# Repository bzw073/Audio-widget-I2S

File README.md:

# Audio-widget-I2S
**Interfata audio USB utilizand un AVR32 pe protocolul I2S**

## Introducere
>
>Inca din timpurile dinaintea erei digitale, consumatorii de audio **asa zisii audiofili** au fost in cautare de metode pentru reducerea la minim a distorsiunilor transmise catre difuzoare,si implicit,percepute de urechea umana.In vremea respectiva,data fiind si complexitatea destul de redusa a dispozitivelor,ideea reducerii distorsiunilor in sisteme era destul de limitata de topologiile propuse,de aceea aparitia sistemelor digitale de procesare in audio a dus la reducerea drastica a neajunsurilor semnalelor analogice.Pentru **puristi** , circuitele digitale si DSP-urile sunt considerate _un sacrilegiu_ adus audiofiliei,dar este unul justificat,deoarece in ciuda complexitatii mai ridicate fata de un circuit analog pur , sistemele digitale sunt mult mai eficiente fata de complementele sale,iar posibilitatea customizarii lor este foarte mare (spre deosebire de un circuit analogic unde,pentru a modifica o caracteristica trebuie regandit tot circuitul,in cazul unui circuit digital cu uC este doar o problema de software).

>Aparitia interfetelor audio s-a facut odata cu dezvoltarea PC-urilor si inregistrarea de muzica/sunete pe medii digitale , in pofida benzilor magnetice si a discurilor de vinil , deoarece era necesara o metoda de redare a sunetelor stocate pe calculatoarele vremii. De altfel,primele asa zise **placi de sunet** si-au facut aparitia prin calculatoare in jurul generatiei 80486 , cand deja exista o oarecare structura de operare stabila pe 16 biti , iar pentru o esantionare simpla a sunetelor erau arhisuficiente instructiunile implementate de Intel in procesoarele respective.
>>_Daca facem referinta la vremurile actuale,se poate spune ca practic nici nu se punea problema de calitate sau termenul de **Hi-Fi** in acele vremuri,dar acele sunete au reprezentat ceea ce urma sa fie boom-ul erei digitale_
>
>Ca si istorie a acestei ere in care traim,se pot scrie foarte multe lucruri deja cunoscute,asa ca voi incerca sa ma concentrez pe esential.

>Ideea de "calitate audio" pe digital a aparut in momentul lansarii pe piata mondiala a CD-ului (acel lucru care acum multora dintre noi ni se pare atat de outdated,ori chiar nu il mai folosim),dar el a avut cea mai mare influenta in aparitia de tehnologii de compresie si codare audio.Ca si concept,ideea de CD a aparut prin anul 1980 ,cand Philips si Sony au incheiat un parteneriat de cercetare in domeniul digital,dorindu-se un mediu de stocare unic transmisibil,care sa aibe un spatiu de stocare a informatiilor mult mai mare decat cel al dischetelor "floppy" si al benzilor magnetice,dar totusi sa nu coste cat un hard disk al vremurilor (memo: un hard disk de tip Winchester avea o capacitate de maxim 128MB , cantarea in jur de 15-20kg si era cam cat un desktop SFF actual ca dimensiuni si costa in jur de ~5.000 de dolari unul?).
>>Standardul CD a fost definitivat in jurul anului 1983,iar in urma intelegerii realizate intre cele 2 concerne se va realiza trecerea industriei audio catre acest mediu.

>Se pune problema "compresiei audio".In a nutshell,algoritmul de compresie audio se refera la un standard de scriere-redare a sunetelor pe calculatoare. Calculatoarele,la momentul respectiv avand sisteme de operare stabile precum UNIX si DOS (vorbind de anii '80,dar regula se aplica si in prezent pe sistemele actuale),pentru a reda sunetele stocate pe medii precum hard-diskul se folosesc de niste software numite **codec** .
>>Codecurile,in esenta,sunt niste pseudo-drivere pe care sistemul de operare le interpreteaza atunci cand se executa in sistem un fisier cu extensia ce corespunde codecului respectiv.
>>Adica,spre exemplu, avem un fisier cu extensia ".mp3" , SO va sti ca la instantierea acestui fisier va trebui sa apeleze un Codec LAME(Lame Ain't an MP3 Encoder - care este o derivatie imbunatatita de-a lungul anilor de diversi programatori din conceptul original gandit de institutul Fraunhofer din Germania).

>De altfel , toate procedeele de redare/compresie si extensiile de sistem au fost posibile datorita codarii PCM (Pulse Code Modulation).
PCM reprezinta transformarea semnalelor analogice in semnale digitale printr-un algoritm de esantionare constanta a amplitudinii semnalului analogic ,iar fiecare esantion este cuantizat la cea mai apropiata valoare dintr-o gama de cuante apropiate.
>>**Codarea PCM prezinta 2 proprietati ce determina calitatea conversiei semnalului original raportat la acesta : rata de esantionare a semnalului si _bit depth_,care reprezinta cantitatea de biti al fiecarui esantion realizat (un CD-Audio prezinta un bit depth de 16 biti per esantion , pe cand un Blu-ray sau DVD-Audio 24 de biti per esantion).**
>>> Extensiile posibile unei compresii PCM sunt ".wav" ,".L16",".PCM",".AIFF",".AU"

>Pe baza codarii/compresiei PCM a fisierelor audio, cei de la Philips au realizat in anul 1986 (si ulterior revizuit in 1996) un protocol de transmisie seriala al datelor audio intre dispozitive / circuite integrate , protocol care inca se foloseste cu succes si in prezent in dispozitivele audio. Este cunoscut sub acronimul I2S sau IIS **Inter-IC Sound** si se bazeaza pe o magistrala sincrona de transmisie de date (clockul de transmisie intre circuite este separat de magistrala de date,deci implicit receptorul nu mai are nevoie de un circuit suplimentar de refacere a frontului de ceas trimis de emitator).
>Protocolul este relativ usor de interpretat, in principal avem de-a face cu 3 semnale : bit clock line(**BCLK**) , word clock line (cunoscut sub denumirea oficiala de 'word select' **WS** sau 'left-right clock' **LRCLK** ) si cel putin o linie de date multiplexata **SD**

>>Adeseori se mai poate intalni peste cele 3 semnale cunoscute inca un semnal de tact (care nu face parte din protocol) cu rolul de a sincroniza operatiile interne ale DAC-urilor cu cele ale controllerului . Este gasit sub acronimul de "Master clock" **MCLK**
>>>Frecventa tipica de lucru se calculeaza dupa formula : **MCLK = 256 * LRCLK**

###### Cum functioneaza protocolul:

>Semnalul de "Word Select" permite dispozitivului receptor sa 'vada' ce canal urmeaza sa fie trimis , deoarece I2S permite ca pe aceeasi linie de date sa fie trimise 2 canale,fiind un semnal cu factor de umplere 50% si frecventa egala cu cea de esantionare a semnalului trimis.
>>**Pentru semnale stereo , in brosura de specificatii a I2S se spune ca semnalul audio de pe canalul stang se transmite pe palierul de 0 al Word Select , iar canalul drept pe palierul de 1 . De obicei , semnalul "Word Select" este sincronizat dupa fronturile cazatoare ale semnalului BCLK , deoarece datele sunt zavorate pe fronturile crescatoare**.
>>
>Se stabileste semnul liniei de date si se codeaza in complement fata de 2 cu primul bit MSB-ul . **Acest lucru permite ca numarul de biti per cadru sa fie arbitrar , fara a fi nevoie de "negociere" intre emitator si receptor **.

## Specificatii montaj:

1.
 a)Microcontroller utilizat:  Atmel AT32UC3A3256 
 >>>  A complete system-on-chip 32-bit AVR microcontroller. It is designed for cost-sensitive embedded applications that require low power consumption, high code density and high performance.

 >>> The microcontroller's Memory Protection Unit (MPU) and fast, flexible interrupt controller support the latest real-time operating systems. Higher computation capabilities are achievable using a rich set of DSP instructions. The device incorporates on-chip flash and SRAM memories for secure and fast access. 64 KBytes of SRAM are directly coupled to the 32-bit AVR UC3 for performance optimization. Two blocks of 32 Kbytes SRAM are independently attached to the high speed bus matrix for real ping-pong management.

 >>> The microcontroller achieves exceptionally high data throughput by combining the multi-layered 32-bit AVR databus,128 KB on-chip SRAM with triple high speed interfaces, multi-channel peripheral, memory-to-memory DMA controller, high-speed USB embedded host, SD/SDIO card, MLC NAND flash with ECC, and SDRAM interfaces.

 >>> This device features 256KB internal high-speed flash and full-duplex multi-channel I2S audio interface.
 
 b) DAC utilizat: PCM5102A

 >>>The PCM510xA devices are a family of monolithic CMOS-integrated circuits that include a stereo digital-to-analog converter and additional support circuitry in a small TSSOP package. The PCM510xA devices use the latest generation of TI’s advanced segment-DAC architecture to achieve excellent dynamic performance and improved tolerance to clock jitter.

 c) Amplificator/buffer iesire folosit : TPA6120
 >>>In applications requiring a high-power output, very high fidelity headphone amplifier, the TPA6120A2 replaces a costly discrete design and allows music, not the amplifier, to be heard. The TPA6120A2’s current-feedback AB amplifier architecture delivers high bandwidth, extremely low noise, and up to 128dB of dynamic range.
 
2.Utilizeaza USB Audio Class 1 / 2.

3.Capabilitati de redare audio pana la 24bit/96kHz (bit depth / sampling rate).

4.Tensiune de alimentare: 5V

5.Consum max: 500mA 

### Constructie montaj:

Contructia se bazeaza pe un design modular , iar in acest sens voi concepe intregul sistem pe 4 placi:
 - una o va constitui interfata emulatoare usb-i2s
 - o placa pentru DAC si , eventual , buffere de iesire
 - o placa pentru amplificatorul final
 - o placa pentru alimentare suplimentara

Ideea conceperii montajului intr-un sistem modular este pentru imbunatatirea "lantului" pe decursul timpului (ex. realizarea unui DAC mai performant din perspectiva SNR / PSRR sau schimbarea unei surse liniare cu una in comutatie sau adaugarea de acumulatori pentru portabilitate etc.)

De altfel,un montaj modular poate presupune o asezare mai buna in cutie si,totodata, un ecranaj mai bun al partilor **mai sensibile** fata de circuitul de alimentare.

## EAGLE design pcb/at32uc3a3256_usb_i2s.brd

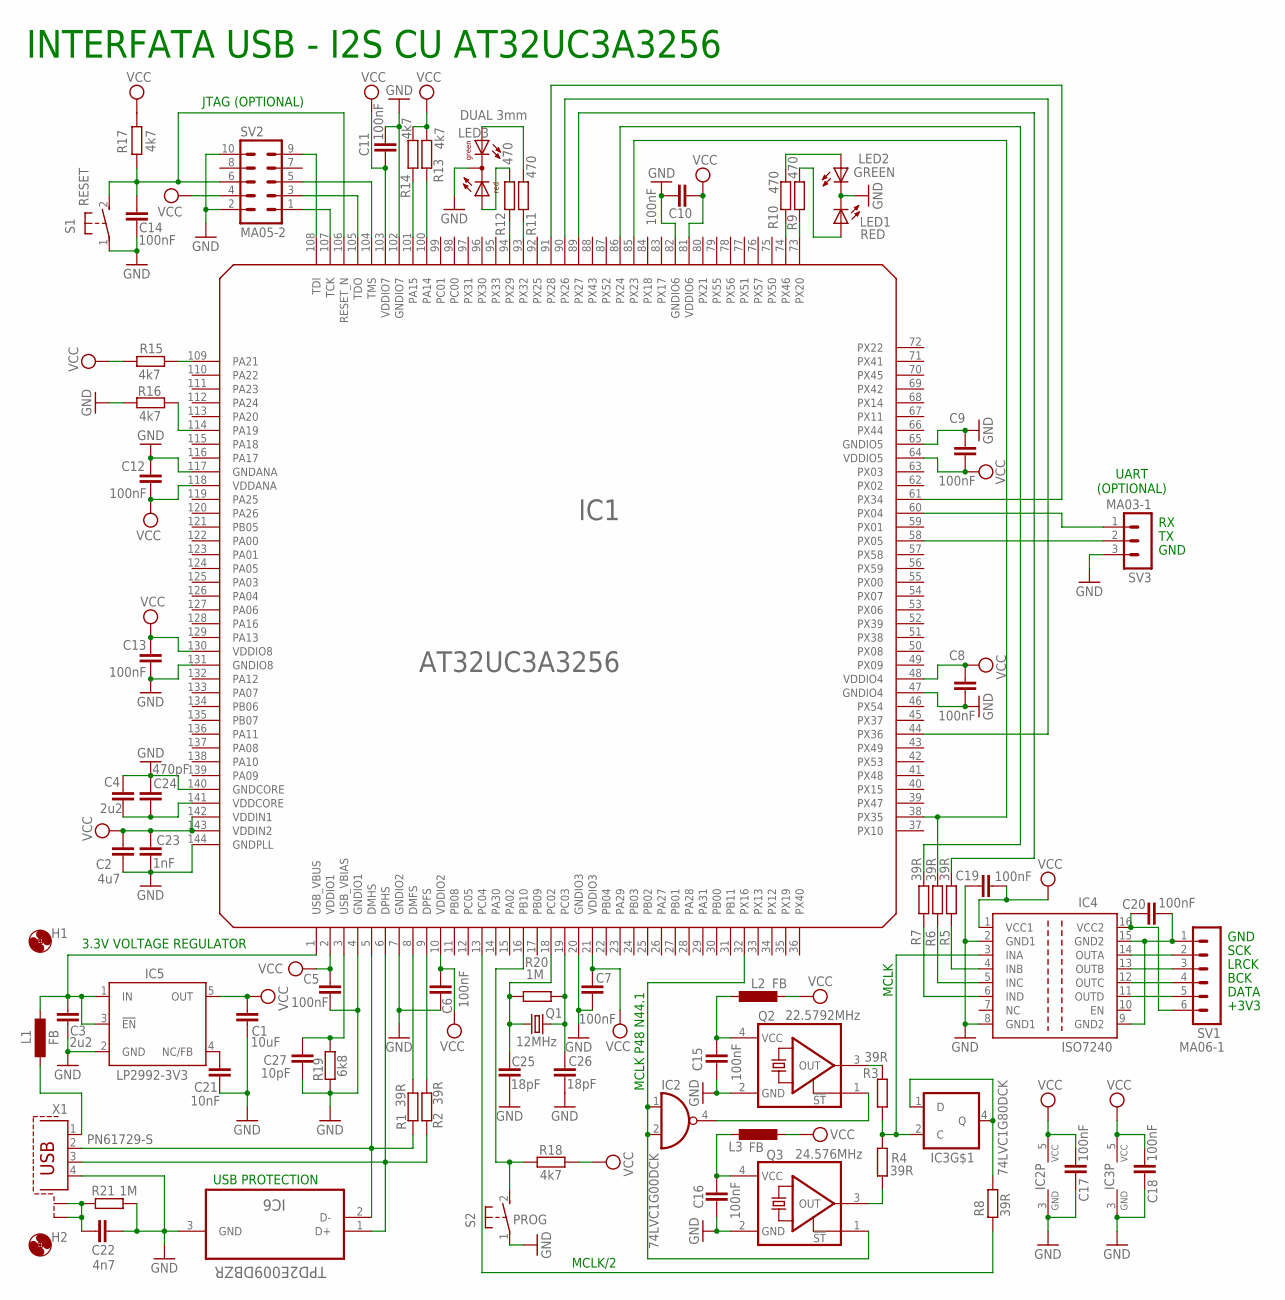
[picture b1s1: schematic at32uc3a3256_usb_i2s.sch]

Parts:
C1: 10uF; C0603
C2: 4u7; C0603
C3, C4: 2u2; C0603
C5, C6, C7, C8, C9, C10, C11, C12, C13, C14, C15, C16, C17, C18, C19, C20: 100nF; C0603
C21: 10nF; C0603
C22: 4n7; C0603
C23: 1nF; C0603
C24: 470pF; C0603
C25, C26: 18pF; C0603
C27: 10pF; C0603
H1, H2: MOUNT-HOLE3.2; 3,2
IC1: AT32UC3A3256; LQFP144
IC2: 74LVC1G00DCK; SC70-5
IC3: 74LVC1G80DCK; SC70-5
IC4: ISO7240; SO-16DW
IC5: LP2992-3V3; SOT23-DBV
IC6: TPD2E009DBZR; SOT95P237X112-3N
L1, L2, L3: FB; L2012C
LED1: RED; CHIPLED_0603
LED2: GREEN; CHIPLED_0603
LED3: DUAL 3mm; DUOLED5MM
Q1: 12MHz; CTS406
Q2: 22.5792MHz; CRYSTAL2.5X2
Q3: 24.576MHz; CRYSTAL2.5X2
R1, R2, R3, R4, R5, R6, R7, R8: 39R; R0603
R9, R10, R11, R12: 470; R0603
R13, R14, R15, R16, R17, R18: 4k7; R0603
R19: 6k8; R0603
R20, R21: 1M; R0603
S1: RESET; SWITCH-KSR
S2: PROG; SWITCH-KSR
SV1: MA06-1
SV2: MA05-2
SV3: MA03-1
X1: PN61729-S

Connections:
AD_LRCK: IC1.44 (PX36), IC1.90 (PX26)
AD_SCLK: IC1.61 (PX34), IC1.91 (PX28)
DA_LRCK: IC1.89 (PX27), R5.2
DA_SCLK: IC1.38 (PX35), IC1.85 (PX23), R6.2
GND: C1.2, C2.2, C3.2, C4.1, C5.2, C6.2, C7.2, C8.2, C9.1, C10.1, C11.1, C12.1, C13.1, C14.2, C15.1, C16.1, C17.2, C18.2, C19.1, C21.2, C22.2, C23.2, C24.1, C25.2, C26.2, C27.2, IC1.4 (GNDIO1), IC1.7 (GNDIO2), IC1.20 (GNDIO3), IC1.47 (GNDIO4), IC1.65 (GNDIO5), IC1.82 (GNDIO6), IC1.102 (GNDIO7), IC1.117 (GNDANA), IC1.131 (GNDIO8), IC1.140 (GNDCORE), IC1.144 (GNDPLL), IC2.3 (GND), IC3.3 (GND), IC4.2 (GND1), IC4.8 (GND1), IC5.2 (GND), IC6.3 (GND), LED1.C, LED2.C, LED3.K (C), Q2.2 (GND), Q3.2 (GND), R16.1, R19.1, R21.2, S1.1, S2.1, SV2.2, SV2.10, SV3.3, X1.4
GND2: C20.2, IC4.9 (GND2), IC4.15 (GND2), SV1.1
GPIO_05_LED2: IC1.94 (PX29), R12.1
GPIO_08_LED1: IC1.93 (PX32), R11.1
LRCK: IC4.4 (INB), R5.1
MCLK: IC3.2 (C), IC4.3 (INA), R3.1, R4.2
MCLK_MCU: IC1.13 (PC04), R8.1
MCLK_P48_N441: IC1.32 (PX16), IC2.1 (I0), IC2.2 (I1), Q3.1 (!ST)
unnamed: C15.2, L2.2, Q2.4 (VCC)
unnamed: IC1.5 (DMHS), IC6.2 (D-), R1.1, X1.2
unnamed: Q3.3 (OUT), R4.1
unnamed: Q2.3 (OUT), R3.2
unnamed: C16.2, L3.2, Q3.4 (VCC)
unnamed: IC1.6 (DPHS), IC6.1 (D+), R2.1, X1.3
unnamed: IC1.8 (DMFS), R1.2
unnamed: C26.1, IC1.19 (PC03), Q1.3 (2), R20.2
unnamed: C25.1, IC1.18 (PC02), Q1.1, R20.1
unnamed: IC1.9 (DPFS), R2.2
unnamed: C4.2, C24.2, IC1.141 (VDDCORE)
unnamed: IC1.108 (TDI), SV2.9
unnamed: IC1.114 (PA19), R16.2
unnamed: C22.1, R21.1, X1.S1, X1.S2
unnamed: C27.1, IC1.3 (USB_VBIAS), R19.2
unnamed: C20.1, IC4.16 (VCC2), SV1.6
unnamed: IC4.14 (OUTA), SV1.2
unnamed: IC4.13 (OUTB), SV1.3
unnamed: IC4.12 (OUTC), SV1.4
unnamed: LED1.A, R9.2
unnamed: LED2.A, R10.2
unnamed: IC1.74 (PX46), R10.1
unnamed: IC1.73 (PX20), R9.1
unnamed: IC1.109 (PA21), R15.2
unnamed: IC1.101 (PA15), R14.1
unnamed: IC1.100 (PA14), R13.1
unnamed: IC4.11 (OUTD), SV1.5
unnamed: IC4.5 (INC), R6.1
unnamed: IC1.86 (PX24), R7.2
unnamed: IC4.6 (IND), R7.1
unnamed: IC3.1 (D), IC3.4 (Q), R8.2
unnamed: L1.1, X1.1
unnamed: LED3.AG, R11.2
unnamed: C21.1, IC5.4 (NC/FB)
unnamed: LED3.AR, R12.2
unnamed: IC2.4 (O), Q2.1 (!ST)
NSRST: C14.1, IC1.106 (RESET_N), R17.1, S1.2, SV2.6
PROG: IC1.16 (PB10), R18.2, S2.2
TCK: IC1.107 (TCK), SV2.1
TDO: IC1.105 (TDO), SV2.3
TMS: IC1.104 (TMS), SV2.5
UART_RX: IC1.60 (PX04), SV3.1
UART_TX: IC1.58 (PX05), SV3.2
VBUS: C3.1, IC1.1 (USB_VBUS), IC5.1 (IN), IC5.3 (!EN), L1.2
VCC: C1.1, C2.1, C5.1, C6.1, C7.1, C8.1, C9.2, C10.2, C11.2, C12.2, C13.2, C17.1, C18.1, C19.2, C23.1, IC1.2 (VDDIO1), IC1.10 (VDDIO2), IC1.21 (VDDIO3), IC1.48 (VDDIO4), IC1.64 (VDDIO5), IC1.81 (VDDIO6), IC1.103 (VDDIO7), IC1.118 (VDDANA), IC1.130 (VDDIO8), IC1.142 (VDDIN1), IC1.143 (VDDIN2), IC2.5 (VCC), IC3.5 (VCC), IC4.1 (VCC1), IC5.5 (OUT), L2.1, L3.1, R13.2, R14.2, R15.1, R17.2, R18.1, SV2.4

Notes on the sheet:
GND
SCK
LRCK
BCK
DATA
+3V3
INTERFATA USB - I2S CU AT32UC3A3256
MCLK
MCLK/2
MCLK P48 N44.1
3.3V VOLTAGE REGULATOR
USB PROTECTION
JTAG (OPTIONAL)
UART (OPTIONAL)

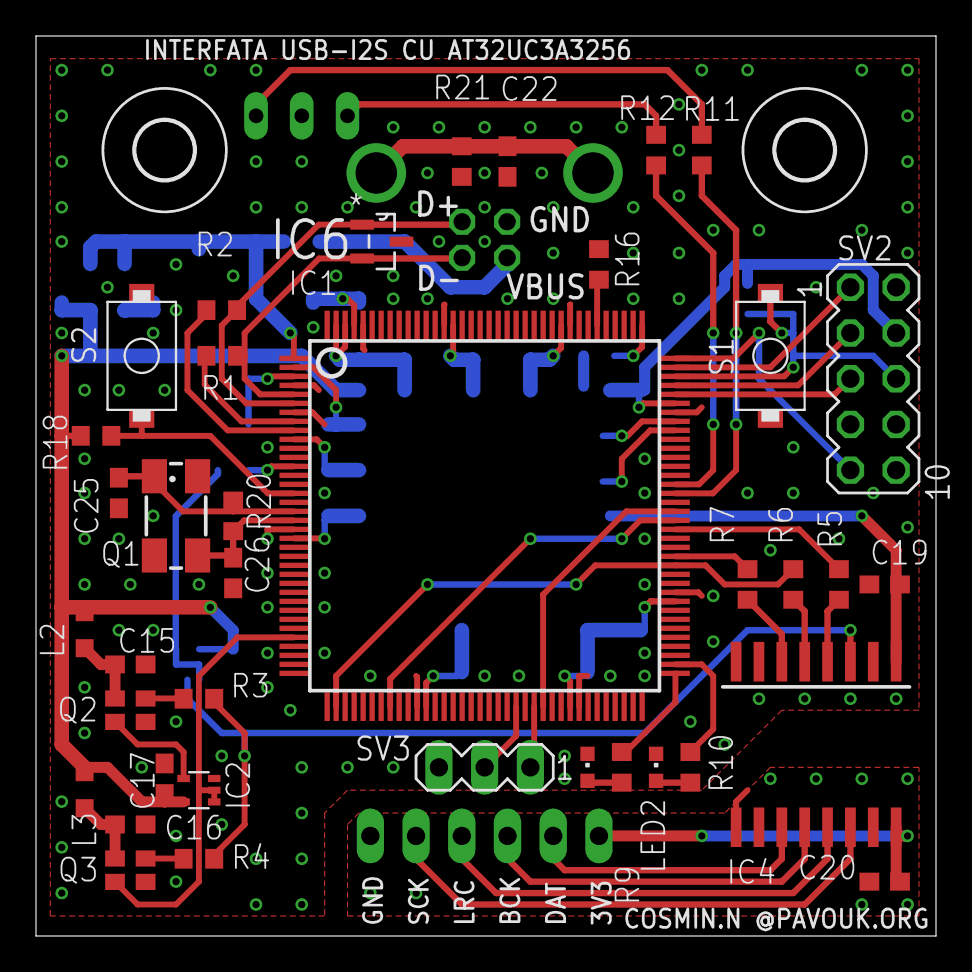
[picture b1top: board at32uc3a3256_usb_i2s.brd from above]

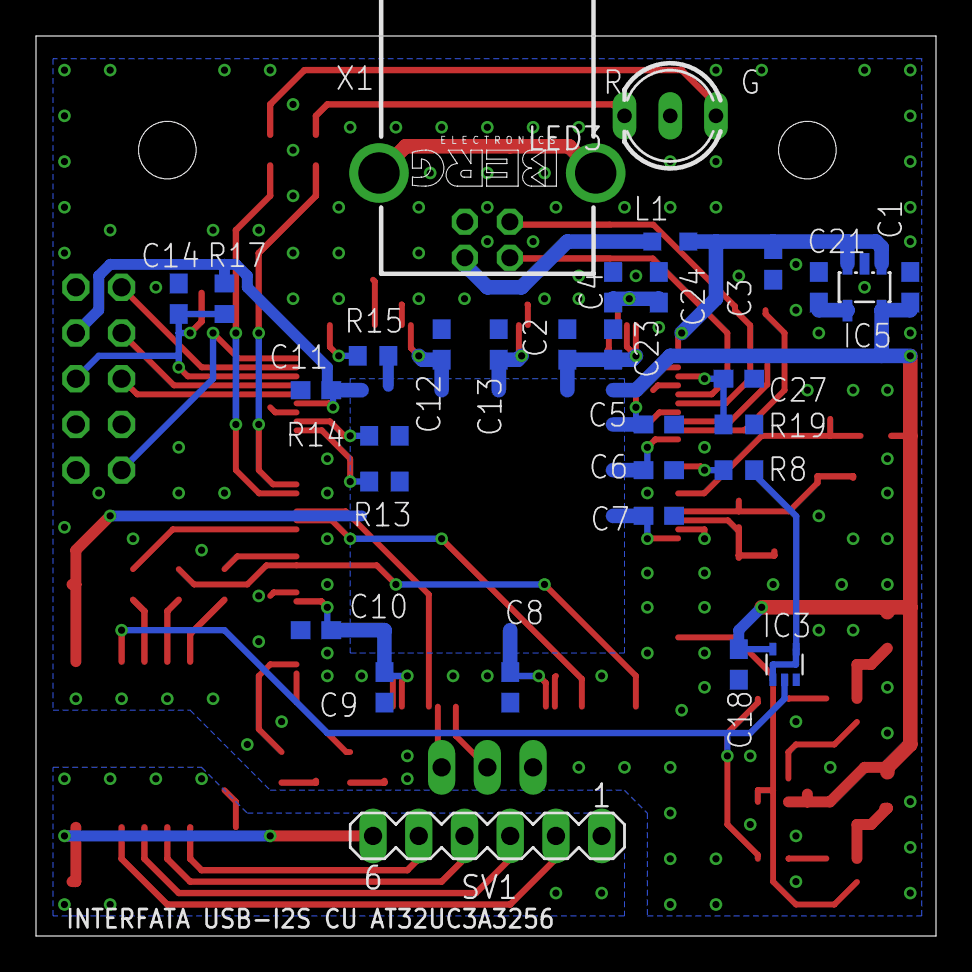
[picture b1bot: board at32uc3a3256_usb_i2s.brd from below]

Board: 2 copper layers, 50.0 x 50.0 mm, 71 parts (31 on the bottom side), 57 nets.

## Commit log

2019-10-15 Added some memo about the project
2019-10-16 Update in memos
2019-10-16 Final update for introduction ; todo spec
2019-10-16 Added official I2S spec sheet
2019-10-22 Added some spec memo
2019-10-22 at32uc3a3256 complete datasheet
2019-10-22 Microchip explanation for emulating I2S protocol
2019-10-26 Create about
2019-10-29 Added schematic for I2S interface
2019-10-29 Updated specs
2019-10-29 added datasheets for dac and amp
2019-10-31 Added circuit construction memos
2019-10-31 Added interface pcb design
